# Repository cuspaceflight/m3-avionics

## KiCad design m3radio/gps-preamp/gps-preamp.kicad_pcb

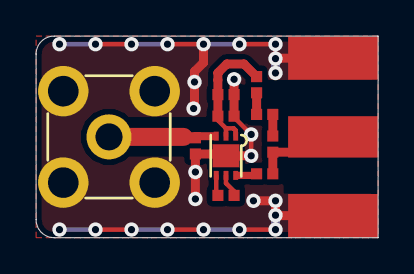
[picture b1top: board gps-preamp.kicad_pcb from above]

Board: 2 copper layers, 19.0 x 11.2 mm, 11 parts (0 on the bottom side), 9 nets.

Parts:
C1: 1µ; 0402
C2: 100n; 0402
C3: 200p; 0402
IC1: BGM1043N7; DFN-6-EP-BGM
L1: 9n1; 0402
L2: 8n2; 0402
L3, L4, L5: 92n; 0402
P2: ANTENNA; SMA-PTH
P3: RECEIVER; SMA-EDGE

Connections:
GND: C1.2, C2.2, IC1.EP, L1.2, P2.2, P3.2
unnamed: C1.1, C2.1, IC1.1, IC1.2, L3.1
unnamed: C3.1, IC1.6
unnamed: C3.2, L5.2, P3.1
unnamed: IC1.3, L1.1, P2.1
unnamed: IC1.4, L2.1
unnamed: IC1.5, L2.2
unnamed: L3.2, L4.1
unnamed: L4.2, L5.1

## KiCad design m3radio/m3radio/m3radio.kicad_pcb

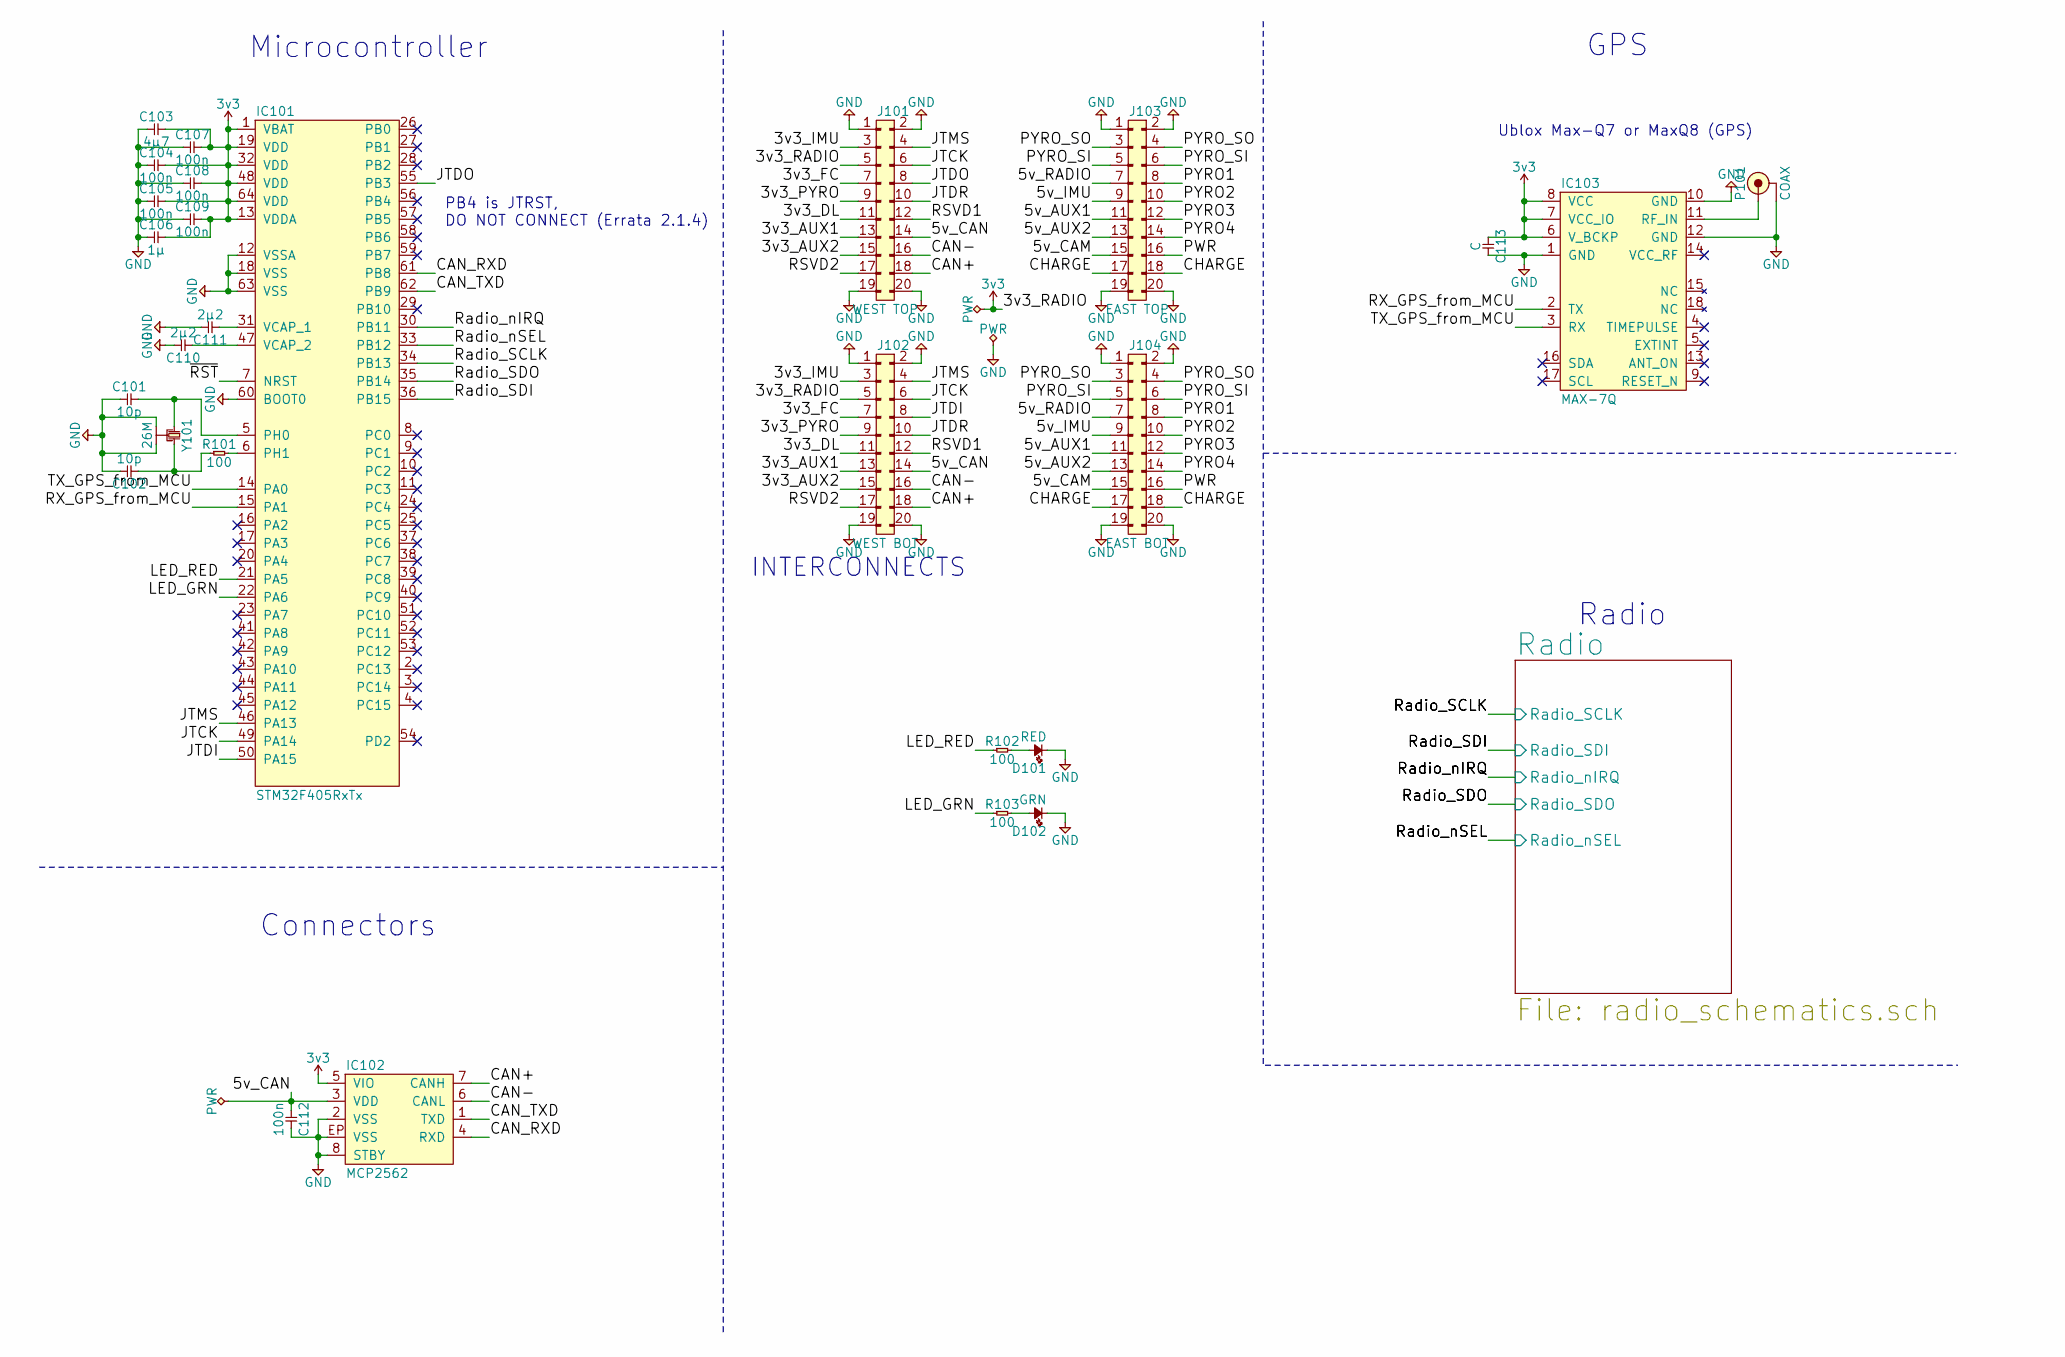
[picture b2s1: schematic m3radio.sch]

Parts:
C101, C102: 10p; 0402; Farnell 2496790
C103: 4µ7; 0402; Farnell 2426952
C104, C105, C107, C108, C109, C112: 100n; 0402; Farnell 2496771
C106: 1µ; 0402; Farnell 2496814
C110, C111: 2µ2; 0402; Farnell 2362088
C113: C; 0402
D101: RED; 0603-LED
D102: GRN; 0603-LED
IC101: STM32F405RxTx; LQFP-64; Farnell 2064363
IC102: MCP2562; DFN-8-EP-MICROCHIP; Farnell 2448755
IC103: MAX-7Q
J101: WEST TOP; TFML-110-02-L-D
J102: WEST BOT; SFML-110-02-L-D-LC
J103: EAST TOP; TFML-110-02-L-D
J104: EAST BOT; SFML-110-02-L-D-LC
P101: COAX; SMA-142-0701-801; Farnell 1608592
R101, R102, R103: 100; 0402; Farnell 9239111
Y101: 26M; XTAL-20x16; Farnell 2506952

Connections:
3v3: C103.2, C104.2, C105.2, C106.2, C107.2, C108.2, C109.2, C113.1, IC101.1 (VBAT), IC101.13 (VDDA), IC101.19 (VDD), IC101.32 (VDD), IC101.48 (VDD), IC101.64 (VDD), IC102.5 (VIO), IC103.6 (V_BCKP), IC103.7 (VCC_IO), IC103.8 (VCC), J101.5, J102.5; also elsewhere on the board
/3v3_AUX1: J101.13, J102.13
/3v3_AUX2: J101.15, J102.15
/3v3_DL: J101.11, J102.11
/3v3_FC: J101.7, J102.7
/3v3_IMU: J101.3, J102.3
/3v3_PYRO: J101.9, J102.9
/5v_AUX1: J103.11, J104.11
/5v_AUX2: J103.13, J104.13
/5v_CAM: J103.15, J104.15
/5v_CAN: C112.1, IC102.3 (VDD), J101.14, J102.14
/5v_IMU: J103.9, J104.9
/5v_RADIO: J103.7, J104.7
/CAN+: IC102.7 (CANH), J101.18, J102.18
/CAN-: IC102.6 (CANL), J101.16, J102.16
/CAN_RXD: IC101.61 (PB8), IC102.4 (RXD)
/CAN_TXD: IC101.62 (PB9), IC102.1 (TXD)
/CHARGE: J103.17, J103.18, J104.17, J104.18
/JTCK: IC101.49 (PA14), J101.6, J102.6
/JTDI: IC101.50 (PA15), J102.8
/JTDO: IC101.55 (PB3), J101.8
/JTDR: J101.10, J102.10
/JTMS: IC101.46 (PA13), J101.4, J102.4
/LED_GRN: IC101.22 (PA6), R103.1
/LED_RED: IC101.21 (PA5), R102.1
/PWR: J103.16, J104.16
/PYRO1: J103.8, J104.8
/PYRO2: J103.10, J104.10
/PYRO3: J103.12, J104.12
/PYRO4: J103.14, J104.14
/PYRO_SI: J103.5, J103.6, J104.5, J104.6
/PYRO_SO: J103.3, J103.4, J104.3, J104.4
/RSVD1: J101.12, J102.12
/RSVD2: J101.17, J102.17
/RX_GPS_from_MCU: IC101.15 (PA1), IC103.2 (TX)
/Radio/Radio_SCLK: IC101.34 (PB13); also elsewhere on the board
/Radio/Radio_SDI: IC101.36 (PB15); also elsewhere on the board
/Radio/Radio_SDO: IC101.35 (PB14); also elsewhere on the board
/Radio/Radio_nIRQ: IC101.30 (PB11); also elsewhere on the board
/Radio/Radio_nSEL: IC101.33 (PB12); also elsewhere on the board
/TX_GPS_from_MCU: IC101.14 (PA0), IC103.3 (RX)
/~RST: IC101.7 (NRST)
GND: C101.1, C102.2, C103.1, C104.1, C105.1, C106.1, C107.1, C108.1, C109.1, C110.2, C111.2, C112.2, C113.2, D101.1, D102.1, IC101.12 (VSSA), IC101.18 (VSS), IC101.60 (BOOT0), IC101.63 (VSS), IC102.2 (VSS), IC102.8 (STBY), IC102.EP (VSS), IC103.1 (GND), IC103.10 (GND), IC103.12 (GND), J101.1, J101.2, J101.19, J101.20, J102.1, J102.2, J102.19, J102.20, J103.1, J103.2, J103.19, J103.20, J104.1, J104.2, J104.19, J104.20, P101.2 (GND), Y101.2, Y101.4; also elsewhere on the board
unnamed: C101.2, IC101.5 (PH0), Y101.1
unnamed: C102.1, R101.1, Y101.3
unnamed: C110.1, IC101.47 (VCAP_2)
unnamed: C111.1, IC101.31 (VCAP_1)
unnamed: D101.2, R102.2
unnamed: D102.2, R103.2
unnamed: IC101.6 (PH1), R101.2
unnamed: IC103.11 (RF_IN), P101.1 (RF)

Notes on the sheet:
Connectors
Microcontroller
Radio
GPS
Ublox Max-Q7 or MaxQ8 (GPS)
INTERCONNECTS
PB4 is JTRST, DO NOT CONNECT (Errata 2.1.4)

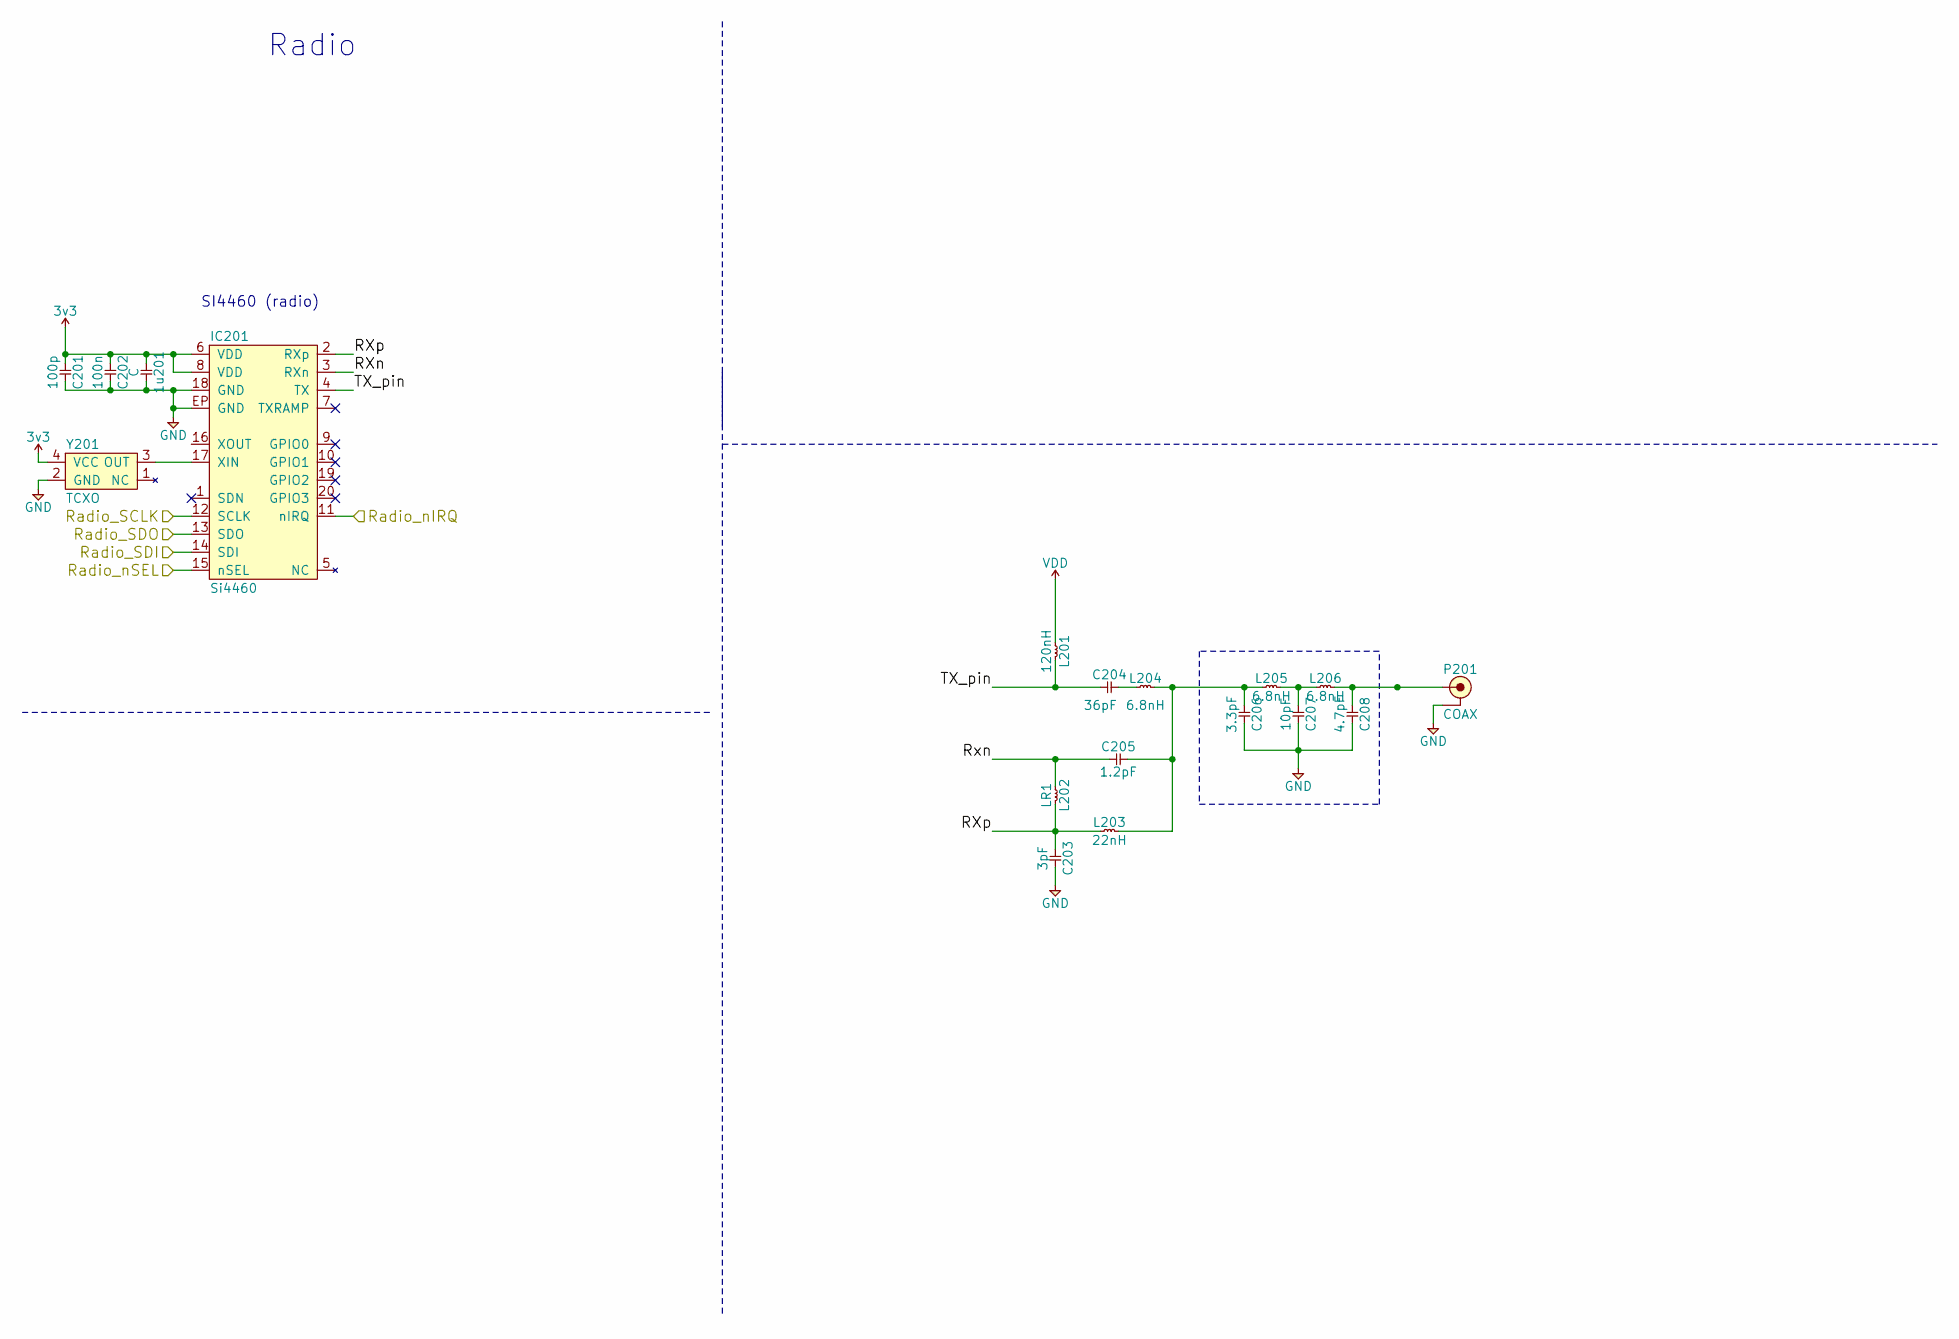
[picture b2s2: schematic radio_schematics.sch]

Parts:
1u201: C; 0402
C201: 100p; 0402
C202: 100n; 0402
C203: 3pF; 0402
C204: 36pF; 0402
C205: 1.2pF; 0402
C206: 3.3pF; 0402
C207: 10pF; 0402
C208: 4.7pF; 0402
IC201: Si4460; QFN-20-EP-SI; Farnell 2462635
L201: 120nH; 0603-L
L202: LR1; 0603-L
L203: 22nH; 0603-L
L204, L205, L206: 6.8nH; 0603-L
P201: COAX; SMA-142-0701-801; Farnell 1608592
Y201: TCXO; Farnell 2405785

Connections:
3v3: 1u201.1, C201.1, C202.1, IC201.6 (VDD), IC201.8 (VDD), Y201.4 (VCC); also elsewhere on the board
/Radio/RXn: C205.1, IC201.3 (RXn), L202.1
/Radio/RXp: C203.1, IC201.2 (RXp), L202.2, L203.1
/Radio/Radio_SCLK: IC201.12 (SCLK); also elsewhere on the board
/Radio/Radio_SDI: IC201.14 (SDI); also elsewhere on the board
/Radio/Radio_SDO: IC201.13 (SDO); also elsewhere on the board
/Radio/Radio_nIRQ: IC201.11 (nIRQ); also elsewhere on the board
/Radio/Radio_nSEL: IC201.15 (nSEL); also elsewhere on the board
/Radio/TX_pin: C204.1, IC201.4 (TX), L201.2
GND: 1u201.2, C201.2, C202.2, C203.2, C206.2, C207.2, C208.2, IC201.18 (GND), IC201.EP (GND), P201.2 (GND), Y201.2 (GND); also elsewhere on the board
unnamed: C204.2, L204.1
unnamed: C205.2, C206.1, L203.2, L204.2, L205.1
unnamed: C207.1, L205.2, L206.1
unnamed: C208.1, L206.2, P201.1 (RF)
unnamed: IC201.17 (XIN), Y201.3 (OUT)
VDD: L201.1

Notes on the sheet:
SI4460 (radio)
Radio

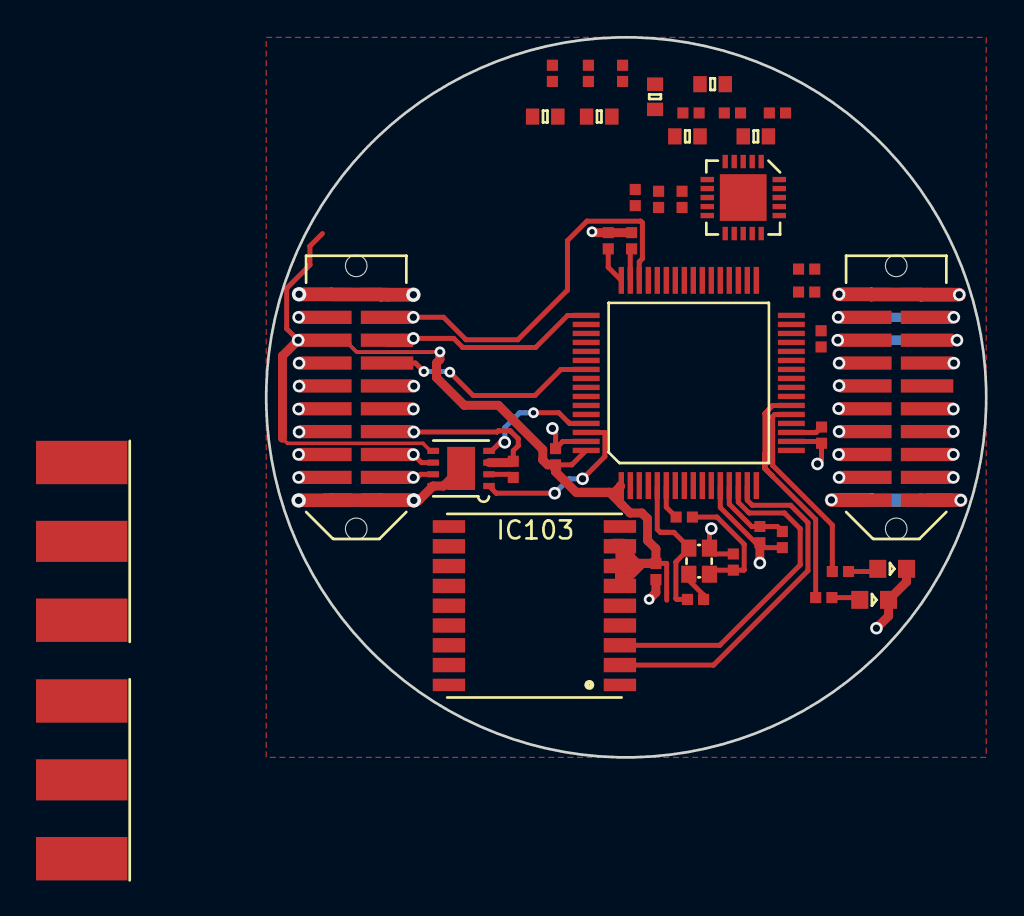
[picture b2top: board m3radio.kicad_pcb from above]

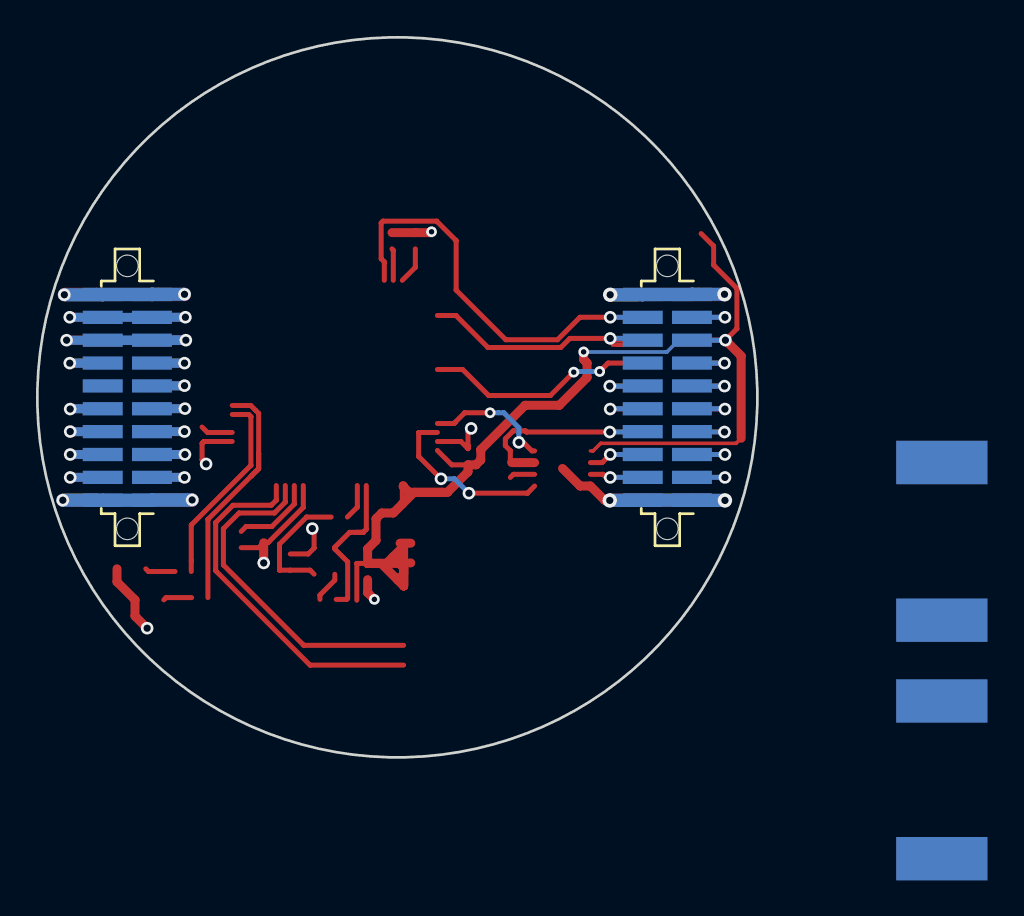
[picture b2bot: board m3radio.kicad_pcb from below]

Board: 2 copper layers, 40.0 x 40.0 mm, 44 parts (2 on the bottom side), 57 nets.
